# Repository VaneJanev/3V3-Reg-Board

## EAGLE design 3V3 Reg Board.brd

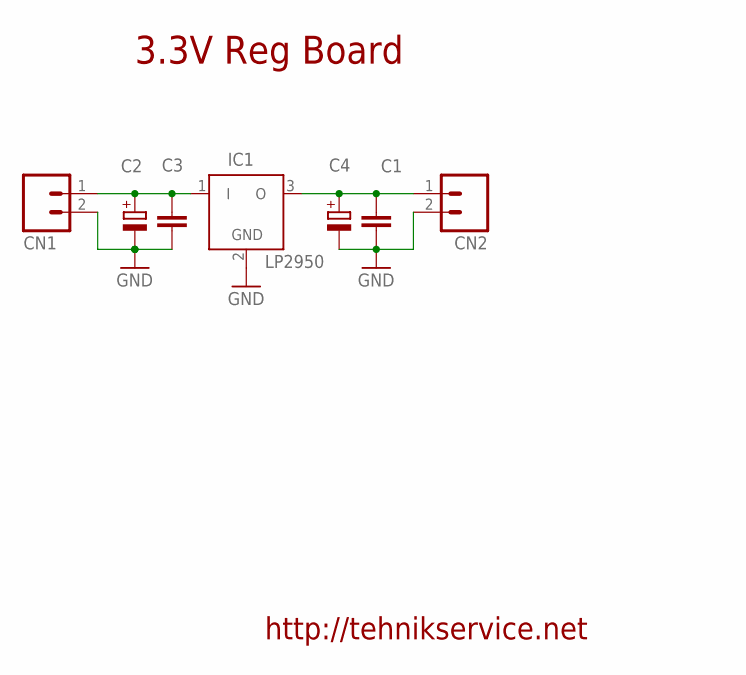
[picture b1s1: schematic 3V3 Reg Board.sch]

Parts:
C1, C2: C-EU025-024X044; C025-024X044
C3, C4: CPOL-EUE1.8-4; E1,8-4
CN1, CN2: M02; 02P
IC1: LP2950; DPACK

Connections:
GND: C1.1, C2.1, C3.-, C4.-, CN1.2, CN2.2, IC1.2 (GND)
unnamed: C2.2, C3.+, CN1.1, IC1.1 (I)
unnamed: C1.2, C4.+, CN2.1, IC1.3 (O)

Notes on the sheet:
http://tehnikservice.net
3.3V Reg Board

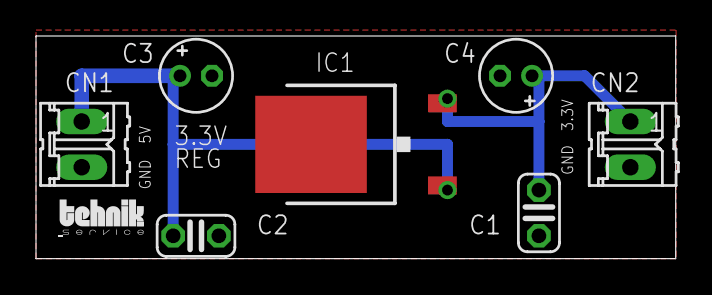
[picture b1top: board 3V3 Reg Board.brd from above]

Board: 2 copper layers, 35.5 x 12.4 mm, 8 parts (0 on the bottom side), 3 nets.

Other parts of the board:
U$1: LOGOT

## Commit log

2015-06-03 :neckbeard: Added .gitattributes
2015-06-03 3V3 Reg Board
